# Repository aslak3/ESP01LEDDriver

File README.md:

# ESP01LEDDriver: a board for attaching an ESP01 to an addressable LED strip

A [schematic](ESP01LEDDriver.pdf) is included here, along with the
[KiCAD](https://www.kicad.org) data files, whcih are in KiCAD 6 format.

## PCB design

The PCB is a trivial 2 layer board.

## Using

After coming across the
[ESP01](https://www.instructables.com/Getting-Started-With-the-ESP8266-ESP-01/)
I was very impressed. It seemed like an excellent solution to problems where a
very small controller board was needed, such as running
[WLED](https://kno.wled.ge) to control addressable LED strips. However the LED
strip attachment board I could find used an odd arrangement of receiving power
by attaching a USB-A plug directly to the board. I wanted to use a power lead of
some description, going to the controller board which then had the LED strip
screwed into it on terminals. As I was ordering some other boards, I thought I
would knock up this board and order it at the same time.

Power can be supplied via 5V on the barell plug, or 5V via a USB-B connector.
The [FTDI
FT231XS](https://ftdichip.com/wp-content/uploads/2021/10/DS_FT231X.pdf) is
optional: if included on the board then it is possible to program the ESP01
in-place via the USB connection. Otherwise it must either be programmed using a
dedicated board, or programmed when attached to this board but via a USB TTL (in
3.3V mode!) UART attached to the four header pins.

In either case, the PROGRAM button can be used to bring up the ESP01 in
programming mode.

## TODO

When time allows I will CAD-up a small printable case for enclosing this board.

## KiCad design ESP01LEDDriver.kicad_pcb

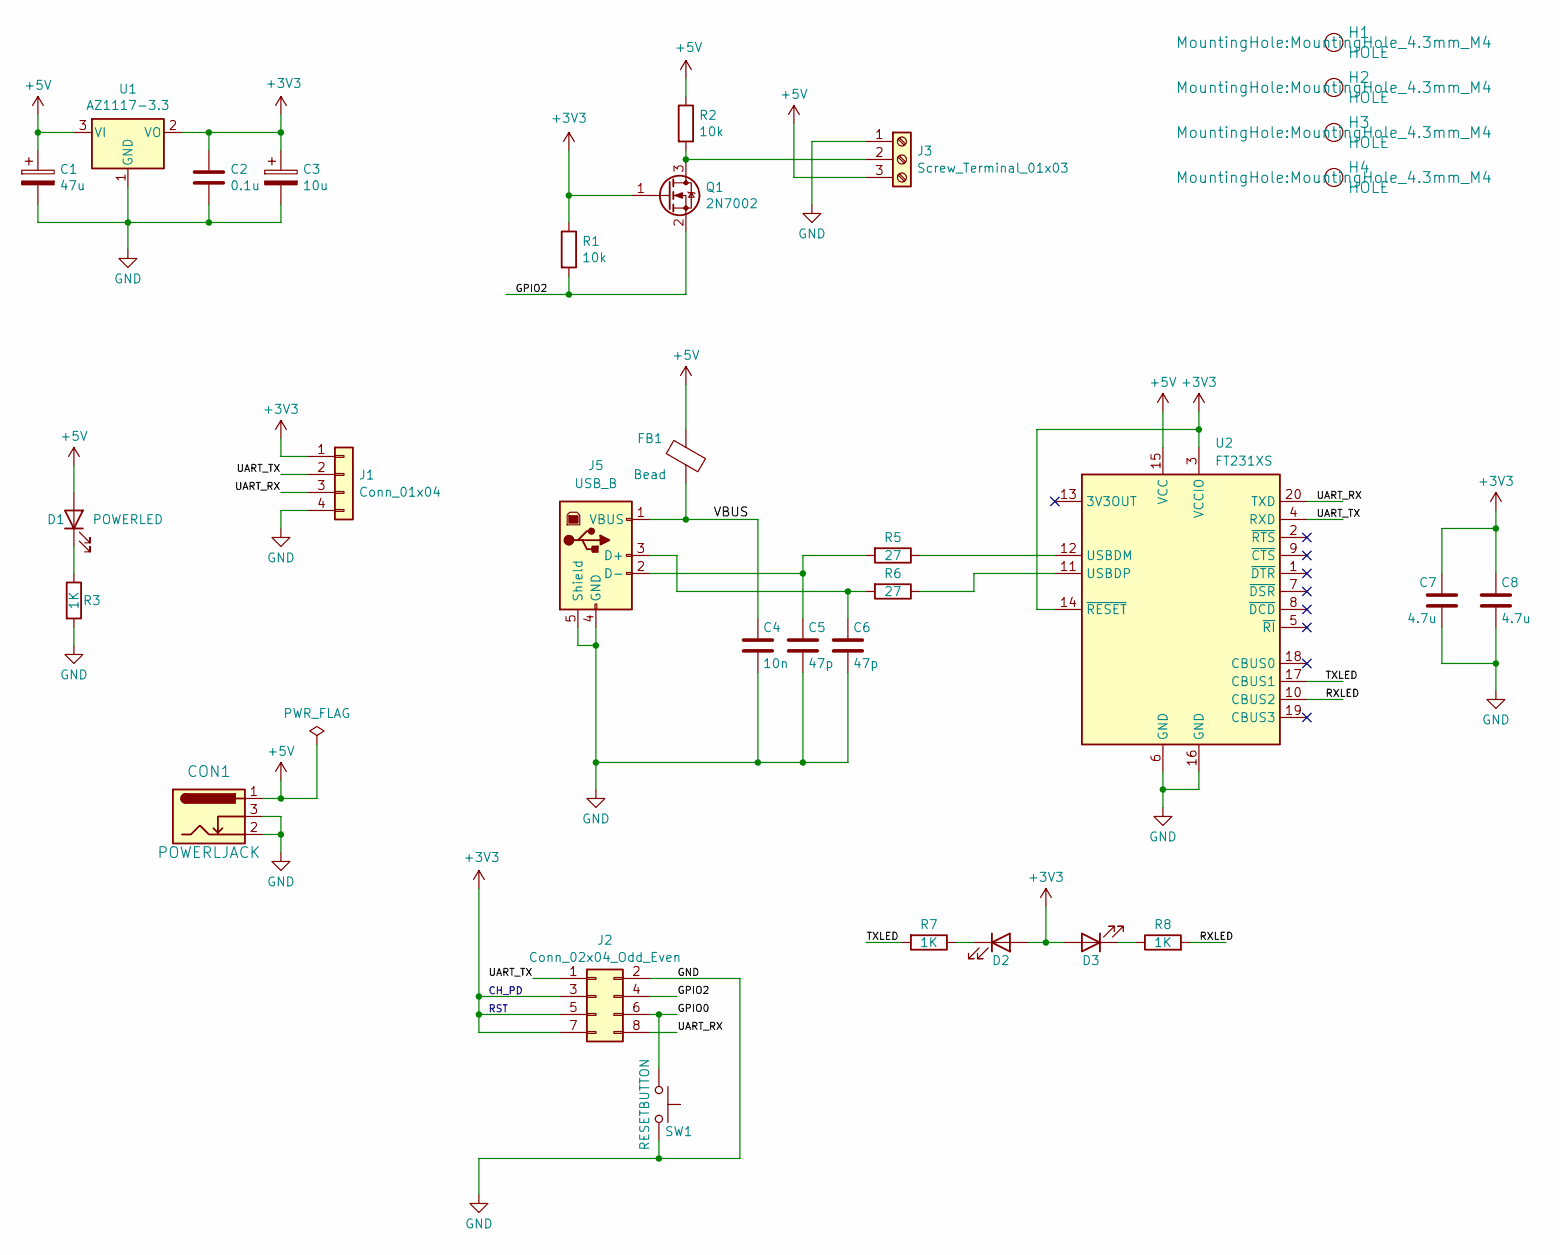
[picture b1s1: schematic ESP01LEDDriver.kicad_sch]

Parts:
C1: 47u; CP_EIA-7343-15_Kemet-W
C2: 0.1u; C_0805_2012Metric
C3: 10u; CP_EIA-3216-10_Kemet-I
C4: 10n; C_0805_2012Metric
C5, C6: 47p; C_0805_2012Metric
C7, C8: 4.7u; C_0805_2012Metric
CON1: POWERLJACK; BarrelJack_Horizontal
D1: POWERLED; LED_1210_3225Metric
D2, D3: UART_LED; LED_1210_3225Metric
FB1: Bead; L_1206_3216Metric
H1, H2, H3, H4: HOLE; MountingHole_4.3mm_M4
J1: Conn_01x04; PinHeader_1x04_P2.54mm_Vertical
J2: Conn_02x04_Odd_Even; PinHeader_2x04_P2.54mm_Vertical
J3: Screw_Terminal_01x03; TerminalBlock_Philmore_TB133_1x03_P5.00mm_Horizontal
J5: USB_B; USB_B_OST_USB-B1HSxx_Horizontal
Q1: 2N7002; SOT-23; LCSC C8545
R1, R2: 10k; R_0805_2012Metric; LCSC C17414
R3, R7, R8: 1K; R_0805_2012Metric
R5, R6: 27; R_0805_2012Metric
SW1: RESETBUTTON; SW_Push_1P1T_NO_CK_KSC6xxJ
U1: AZ1117-3.3; SOT-223-3_TabPin2
U2: FT231XS; SSOP-20_3.9x8.7mm_P0.635mm

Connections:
+3V3: C2.1, C3.1, C7.1, C8.1, D2.2 (A), D3.2 (A), J1.1, J2.3, J2.5, J2.7, Q1.1 (G), R1.1, U1.2 (VO), U2.3 (VCCIO), U2.14 (~RESET)
+5V: C1.1, CON1.1, D1.2 (A), FB1.1, J3.3, R2.1, U1.3 (VI), U2.15 (VCC)
/GPIO0: J2.6, SW1.1
/GPIO2: J2.4, Q1.2 (S), R1.2
/RXLED: R8.2, U2.10 (CBUS2)
/TXLED: R7.2, U2.17 (CBUS1)
/UART_RX: J1.3, J2.8, U2.20 (TXD)
/UART_TX: J1.2, J2.1, U2.4 (RXD)
/VBUS: C4.1, FB1.2, J5.1 (VBUS)
GND: C1.2, C2.2, C3.2, C4.2, C5.2, C6.2, C7.2, C8.2, CON1.2, CON1.3, J1.4, J2.2, J3.1, J5.4 (GND), J5.5 (Shield), R3.2, SW1.2, U1.1 (GND), U2.6 (GND), U2.16 (GND)
unnamed: D1.1 (K), R3.1
unnamed: D2.1 (K), R7.1
unnamed: D3.1 (K), R8.1
unnamed: J3.2, Q1.3 (D), R2.2
unnamed: C6.1, J5.3 (D+), R6.2
unnamed: C5.1, J5.2 (D-), R5.2
unnamed: R5.1, U2.12 (USBDM)
unnamed: R6.1, U2.11 (USBDP)

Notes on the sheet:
RST
CH_PD

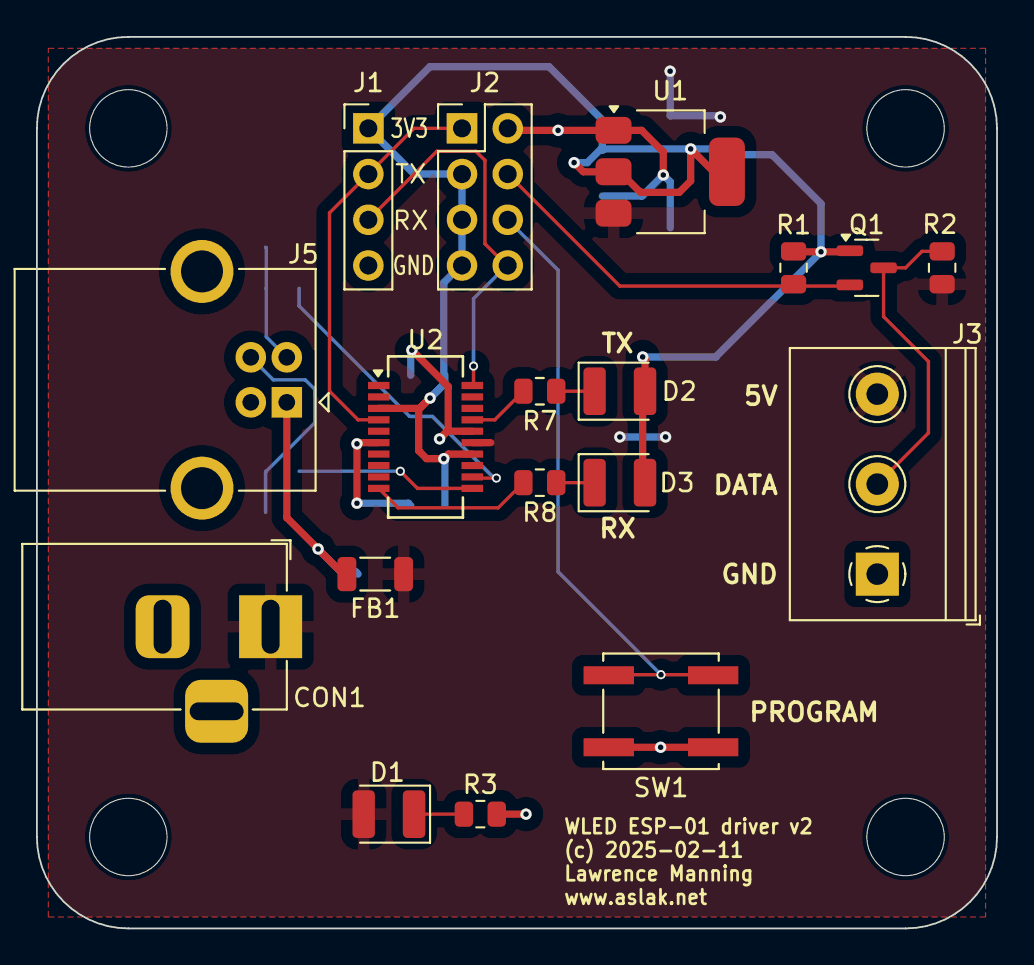
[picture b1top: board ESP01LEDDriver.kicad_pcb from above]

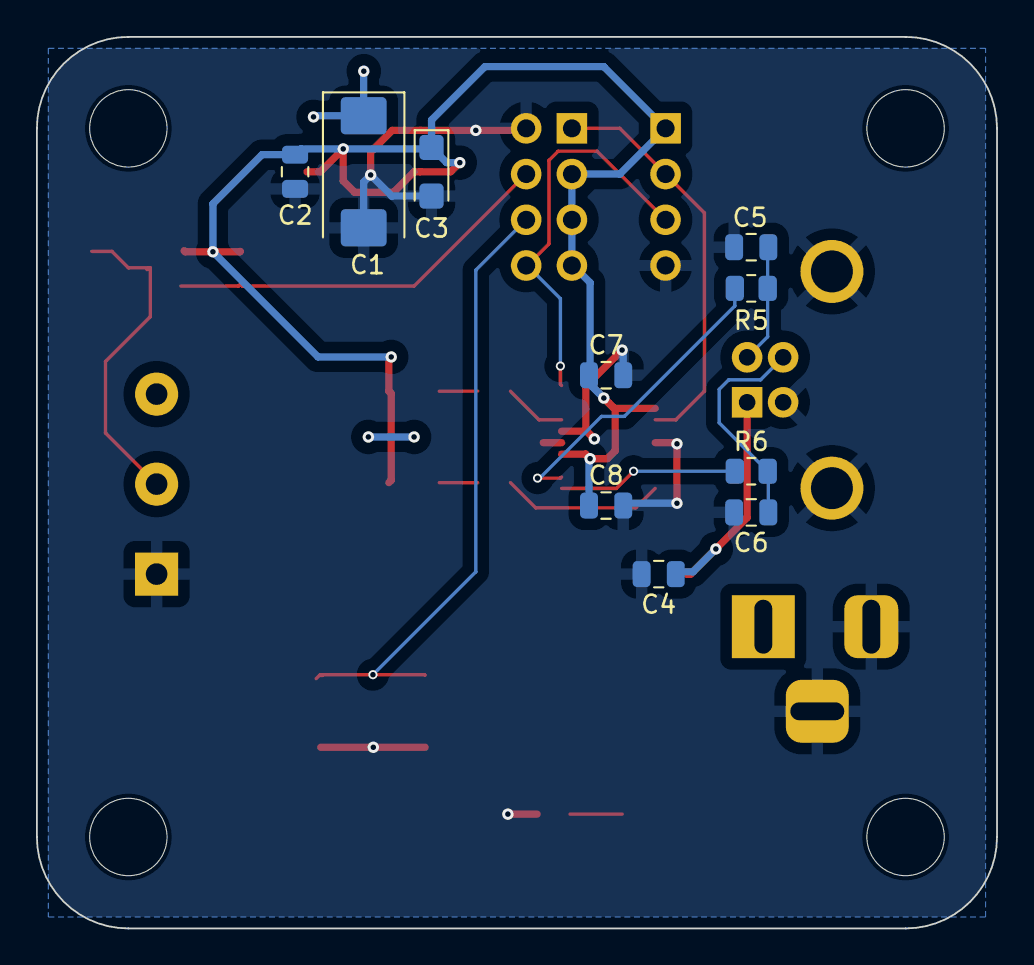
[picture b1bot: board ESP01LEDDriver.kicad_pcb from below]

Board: 2 copper layers, 53.3 x 49.5 mm, 32 parts (10 on the bottom side), 18 nets.

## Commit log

2025-03-31 v2: added an FTDI IC for programming the ESP01 in place
    This part is optional: if included on a built up board then the ESP01 can
    be programmed without removing it from the board or using a USB UART
    attached to the header pins.
    Thanks to Phil Mehew (www.mehew.net) for this suggestion!

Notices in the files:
ESP01LEDDriver.kicad_pcb:
(c) 2025-02-11
